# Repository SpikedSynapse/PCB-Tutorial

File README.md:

# PCB-Tutorial

This is a combo attempt to learn gitHub & learn to build PCBs

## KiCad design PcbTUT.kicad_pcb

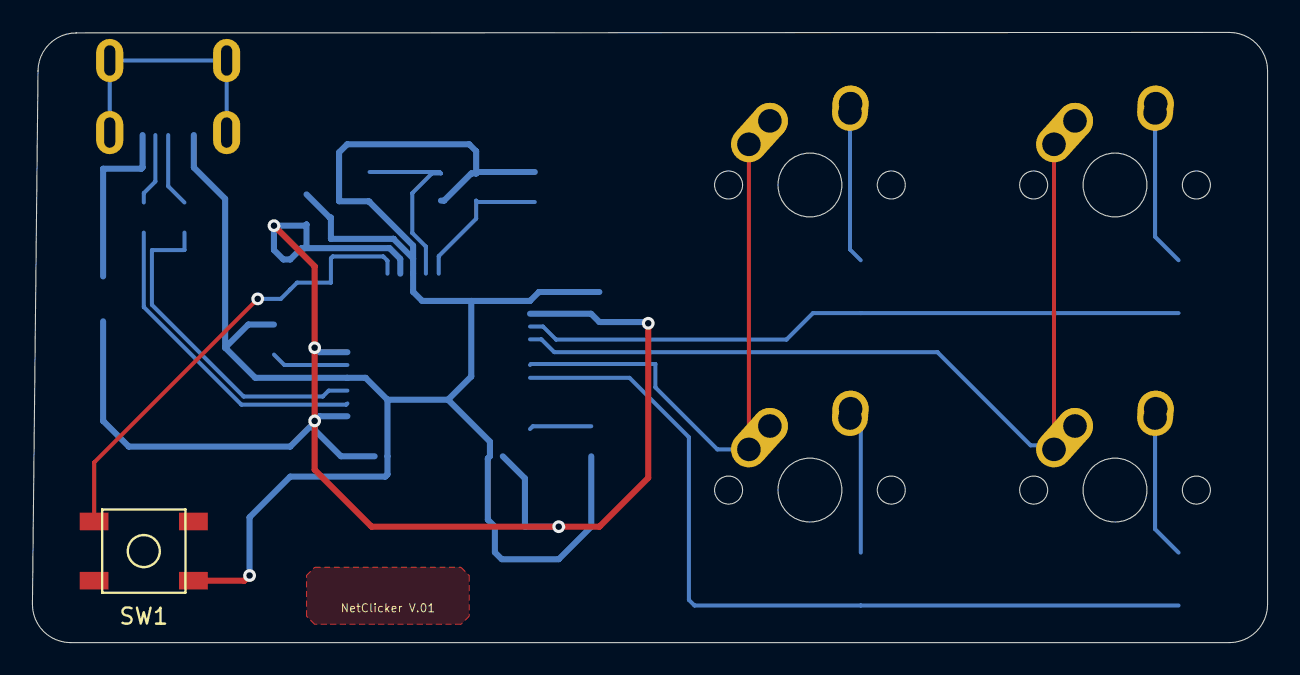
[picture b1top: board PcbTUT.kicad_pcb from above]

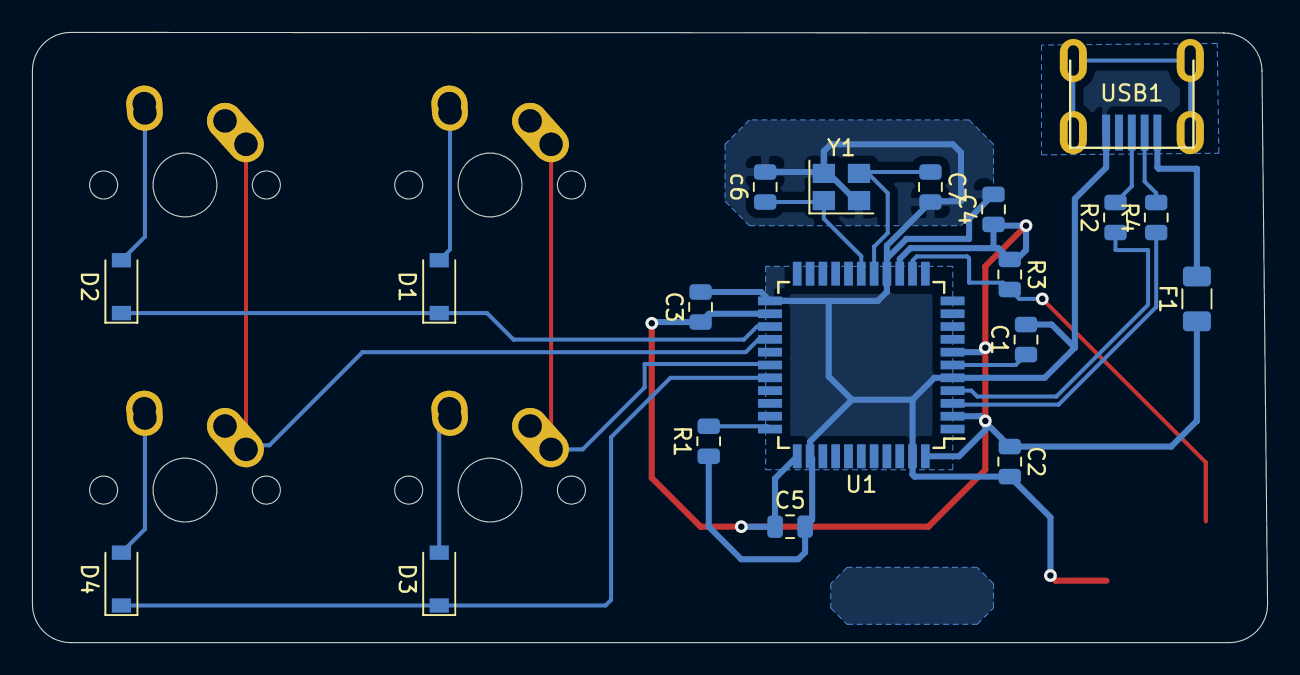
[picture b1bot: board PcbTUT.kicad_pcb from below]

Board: 2 copper layers, 77.1 x 38.1 mm, 24 parts (19 on the bottom side), 20 nets.

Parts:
C1: 1uf; C_0805_2012Metric
C2, C3, C4: .01uf; C_0805_2012Metric
C5: 10uf; C_0805_2012Metric
C7: 22pF; C_0805_2012Metric
D1, D2, D3, D4: D_Small; D_SOD-123
F1: 500mA; Fuse_1206_3216Metric
MX0, MX1, MX2, MX3: MX-NoLED; MX-1U-NoLED
R1, R3: 10k; R_0805_2012Metric
R2, R4: 22k; R_0805_2012Metric
SW1: SW_Push; SKQG-1155865
U1: ATmega32U4-AU; TQFP-44_10x10mm_P0.8mm
USB1: Molex-0548190589
Y1: 16Mhz; Crystal_SMD_3225-4Pin_3.2x2.5mm
c6: 22pF; C_0805_2012Metric

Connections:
+5V: C2.1, C3.1, C4.1, C5.1, F1.1, R3.1, U1.2, U1.7, U1.14, U1.24, U1.34, U1.44
COL0: MX0.1, MX2.1, U1.28
COL1: MX1.1, MX3.1, U1.26
D+: R2.2, USB1.3
D-: R4.2, USB1.4
GND: C1.2, C2.2, C3.2, C4.2, C5.2, C7.2, R1.1, SW1.1, U1.5, U1.15, U1.23, U1.35, U1.43, USB1.1, Y1.2, Y1.4, c6.2
unnamed: C1.1, U1.6
unnamed: C7.1, U1.16, Y1.3
unnamed: D1.2, MX0.2
unnamed: D2.2, MX1.2
unnamed: D3.2, MX2.2
unnamed: D4.2, MX3.2
unnamed: R1.2, U1.33
unnamed: R2.1, U1.4
unnamed: R3.2, SW1.2, U1.13
unnamed: R4.1, U1.3
unnamed: U1.17, Y1.1, c6.1
ROW0: D1.1, D2.1, U1.25
ROW1: D3.1, D4.1, U1.29
VCC: F1.2, USB1.5

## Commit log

2020-06-27 learning about kicad
2020-06-27 Add submodules
2020-06-27 up to step 7
2020-06-28 Asigned Footprints
2020-06-28 route pcb
2020-06-28 Finalized v.01
